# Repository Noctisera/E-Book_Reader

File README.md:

# OpenBook Reader

## 📘 Introduction  
**OpenBook Reader** is an open-source hardware project focused on delivering a practical, low-cost e-book device. Its primary aim is to build the physical design assets—such as schematics, board layouts, and casing models—needed for manufacturing the device according to system-level specs.

This initiative includes:
- Circuit design and layout.
- PCB preparation for fabrication.
- CAD models for enclosure and hardware integration.

---

## 🔧 Project Contents

This repository contains everything needed to bring the device to life, from electronics to mechanical files. Key folders include:

- **Electronics Design**
  - Circuit schematics  
  - Board layout data  
- **Fabrication Files**
  - Manufacturing exports (e.g., Gerbers)  
  - Assembly references (e.g., BOM, placement files)  
- **CAD Assets**
  - Mechanical parts in 3D format (STEP, Fusion360)  
- **Miscellaneous**
  - Licensing information  
  - Documentation  

---

## 📦 Components Summary

### Block Diagram

Below is a selection of the main components used in the hardware design. For each, you’ll find supplier and datasheet links for reference.

## Bill of Materials (BOM)

| Component                       | Link                                                                                                | Datasheet                                                                                             |
| :------------------------------ | :-------------------------------------------------------------------------------------------------- | :------------------------------------------------------------------------------------------------------ |
| ESP32-C6 WROOM-1-N8             | [SnapMagic](https://www.snapeda.com/parts/ESP32-C6-WROOM-1-N8/Espressif+Systems/view-part/?ref=eda) | [Datasheet](https://www.snapeda.com/parts/ESP32-C6-WROOM-1-N8/Espressif%20Systems/datasheet/)       |
| ESP32C6 Varistor 1812           | [Mouser](https://ro.mouser.com/ProductDetail/EPCOS-TDK/B72520T0350K062?qs=dEfas%2FXlABIszF52uu7vrg%3D%3D) | [Datasheet](https://www.tdk-electronics.tdk.com/inf/75/db/CTVS_14/Surge_protection_series.pdf)     |
| ESP32 WROVER 0805 Capacitor     | [Mouser](https://ro.mouser.com/ProductDetail/KYOCERA-AVX/SD0805S020S1R0?qs=jCA%252BPfw4LHbpkAoSnwrdjw%3D%3D) | [Datasheet](https://ro.mouser.com/datasheet/2/40/schottky-3165252.pdf)                               |
| ESP32 WROVER BME680 Sensor      | [SnapMagic](https://www.snapeda.com/parts/BME680/Bosch/view-part/?welcome=home)                      | [Datasheet](https://www.snapeda.com/parts/BME680/Bosch%20Sensortec/datasheet/)                           |
| ESP32 WROVER MCP73831 Power Management | [Mouser](https://eu.mouser.com/ProductDetail/Microchip-Technology/MCP73831T-2ACI-OT?qs=yUQqVecv4qvbBQBGbHx0Mw%3D%3D) | [Datasheet](https://eu.mouser.com/datasheet/2/268/MCP73831_Family_Data_Sheet_DS20001984H-3441711.pdf) |
| ESP32 WROVER P-Channel MOSFET   | [Component Search Engine](https://componentsearchengine.com/part-view/DMG2305UX-7/Diodes%20Incorporated) | [Datasheet](https://www.diodes.com//assets/Datasheets/DMG2305UX.pdf)                                  |
| LED Chip 0603                   | [SnapMagic](https://www.snapeda.com/parts/KP-1608SURCK/Kingbright/view-part/?ref=search&t=LED%200603) | [Datasheet](https://www.snapeda.com/parts/KP-1608SURCK/Kingbright/datasheet/)                           |
| SJ                              | [GrabCad](https://grabcad.com/library/solder-jumpers-1)                                             | [Datasheet](https://www.youtube.com/watch?v=dQw4w9WgXcQ)                                                 |
| LTSPICE Resistor 0402           | [Component Search Engine](https://componentsearchengine.com/part-view/R0402%201%25%20100%20K%20(RC0402FR-07100KL)/YAGEO) | [Datasheet](https://www.yageo.com/upload/media/product/products/datasheet/rchip/PYu-RC_Group_51_RoHS_L_12.pdf) |
| RCL CPOL 3528                   | [SnapMagic](https://www.snapeda.com/parts/TAJB475K025RNJ/AVX/view-part/?ref=dk&t=capacitor%203528&con_ref=None) | [Datasheet](https://s3.amazonaws.com/snapeda/datasheet/TAJB475K025RNJ_AVX.pdf)                       |
| 112A-TAAR-R03                   | [Comet](https://store.comet.srl.ro/Catalogue/Product/43497/)                                       | [Datasheet](https://store.comet.bg/download-file.php?id=27596)                                       |
| Capacitor 0402                  | [Component Search Engine](https://componentsearchengine.com/part-view/CC0402MRX5R5BB106/YAGEO)      | [Datasheet](https://componentsearchengine.com/Datasheets/2/CC0402MRX5R5BB106.pdf)                      |
| 744043680 IND                   | [Mouser](https://eu.mouser.com/ProductDetail/Wurth-Elektronik/744043680?qs=PGXP4M47uW6VkZq%252BkzjrHA%3D%3D) | [Datasheet](https://www.we-online.com/components/products/datasheet/744043680.pdf)                   |
| BD5229G-TR                      | [Component Search Engine](https://componentsearchengine.com/part-view/BD5229G-TR/ROHM%20Semiconductor) | [Datasheet](https://datasheet.datasheetarchive.com/originals/distributors/Datasheets_SAMA/f2b9741ef86007909f138d561a359946.pdf) |
| Custom Button                   | [Panasonic](https://industry.panasonic.com/global/en/products/control/switch/light-touch/number/evqpuj02k) | [Datasheet](https://industry.panasonic.com/global/en/downloads?tab=catalog&small_g_cd=203&part_no=EVQPUJ02K&q=RVZRUFVKMDJLJTdDMTMlN0MyMDMlN0MzNDU5JTdDMSU3QyU3QzIlN0M%3D) |
| CPH3225A                        | [SnapMagic](https://www.snapeda.com/parts/CPH3225A/Seiko+Instruments/view-part/?ref=eda)           | [Datasheet](https://www.snapeda.com/parts/CPH3225A/Seiko%20Instruments/datasheet/)                       |
| DS3231SN RTC                    | [SnapMagic](https://www.snapeda.com/parts/DS3231SN%23/Analog+Devices/view-part/?ref=eda)          | [Datasheet](https://www.snapeda.com/parts/DS3231SN%23/Analog%20Devices/datasheet/)                      |
| FH34SRJ-24S-0.5SH Connector     | [Component Search Engine](https://componentsearchengine.com/part-view/FH34SRJ-24S-0.5SH(99)/Hirose) | [Datasheet](https://www.hirose.com/en/product/document?clcode=CL0580-1255-6-99&productname=FH34SRJ-24S-0.5SH(99)&series=FH34SRJ&documenttype=2DDrawing&lang=en&documentid=0000990903) |
| MAX17048G+T10 Battery Fuel Gauge | [SnapMagic](https://www.snapeda.com/parts/MAX17048G+T10/Analog+Devices/view-part/?ref=eda)         | [Datasheet](https://www.snapeda.com/parts/MAX17048G+T10/Analog%20Devices/datasheet/)                    |
| MBR0530 Schottky Diode         | [SnapMagic](https://www.snapeda.com/parts/MBR0530/Onsemi/view-part/?ref=eda)                      | [Datasheet](https://www.snapeda.com/parts/MBR0530/ON%20Semiconductor/datasheet/)                         |
| PGB1010603MR Inductor          | [SnapMagic](https://www.snapeda.com/parts/PGB1010603MR/Littelfuse/view-part/?ref=eda)              | [Datasheet](https://www.snapeda.com/parts/PGB1010603MR/Littelfuse%20Inc./datasheet/)                     |
| QWIIC Connector                 | [Mouser](https://eu.mouser.com/ProductDetail/Adafruit/4208?qs=PzGy0jfpSMtbScLbr0L5dw%3D%3D)         | [Datasheet](https://www.youtube.com/watch?v=dQw4w9WgXcQ)                                                 |
| USB4110-GF-A USB Hub            | [Component Search Engine](https://componentsearchengine.com/part-view/USB4110-GF-A/GCT%20(GLOBAL%20CONNECTOR%20TECHNOLOGY)) | [Datasheet](https://gct.co/files/drawings/usb4110.pdf)                                                 |
| SI1308EDL-T1-GE3 MOSFET         | [SnapMagic](https://www.snapeda.com/parts/SI1308EDL-T1-GE3/Vishay+Siliconix/view-part/?ref=eda)   | [Datasheet](https://www.youtube.com/watch?v=dQw4w9WgXcQ)                                                 |
| TPTP20R                         | [Comet](https://easyeda.com/component/7524403feb2642ac9f9f26dfb93ceacf)                            | [Datasheet](https://easyeda.com/component/7524403feb2642ac9f9f26dfb93ceacf)                              |
| USBLC6-2SC6Y USB Surge Protection | [SnapMagic](https://www.snapeda.com/parts/USBLC6-2SC6Y/STMicroelectronics/view-part/?ref=eda)    | [Datasheet](https://www.snapeda.com/parts/USBLC6-2SC6Y/STMicroelectronics/datasheet/)                   |
| W25Q512JVEIQ Flash Memory       | [SnapMagic](https://www.snapeda.com/parts/W25Q512JVEIQ/Winbond+Electronics/view-part/?ref=eda)     | [Datasheet](https://www.snapeda.com/parts/W25Q512JVEIQ/Winbond%20Electronics/datasheet/)                |
| XC6220A331MR-G Voltage Regulator | [Component Search Engine](https://componentsearchengine.com/part-view/XC6220A331MR-G/Torex)      | [Datasheet](https://product.torexsemi.com/system/files/series/xc6220.pdf)                               |

---

## 🧠 Key Modules and Functionality

### 🟡 Power System  
- **Battery:** Rechargeable Li-Po providing 3.7V, 1800mAh capacity.  
- **Charger:** Manages safe charging through USB-C.  
- **Regulation:** LDOs provide clean power to different system sections.

### 🔲 Display Unit  
- **Type:** 7.5-inch e-paper screen (black & white).  
- **Comms:** SPI-based, ultra-low-power refresh.

### 🎛 Microcontroller  
- **Model:** ESP32-C6  
- **Role:** Central processor managing all I/O, display, memory, and sensors.  
- **Connectivity:** Offers Wi-Fi and Bluetooth for syncing or updates.

### 🌦 Environmental Sensor  
- **Chip:** BME688  
- **Function:** Captures environmental data (temp, pressure, humidity, gas).

### 🕒 Real-Time Clock  
- **RTC:** DS3231  
- **Use Case:** Keeps time even without power—great for tracking usage.

### 💾 Storage  
- **Flash Memory:** For storing firmware and runtime data.  
- **SD Card Support:** Optional external storage for large file handling (e.g. e-books).

### 🧩 Expandability  
- **Connectors:** I2C/SPI breakout headers support add-on modules.  
- **Test Points:** Available for programming, debugging, and diagnostics.

---

## 🔌 Interfaces & I/O

| Interface | Purpose |
|----------|---------|
| **SPI**  | Display, SD Card, Flash Memory |
| **I2C**  | Sensor, RTC |
| **USB-C**| Charging & data |
| **GPIO** | Button inputs, status indicators |

---

## 📃 License  
This project is released under the MIT License—feel free to use, remix, and contribute.

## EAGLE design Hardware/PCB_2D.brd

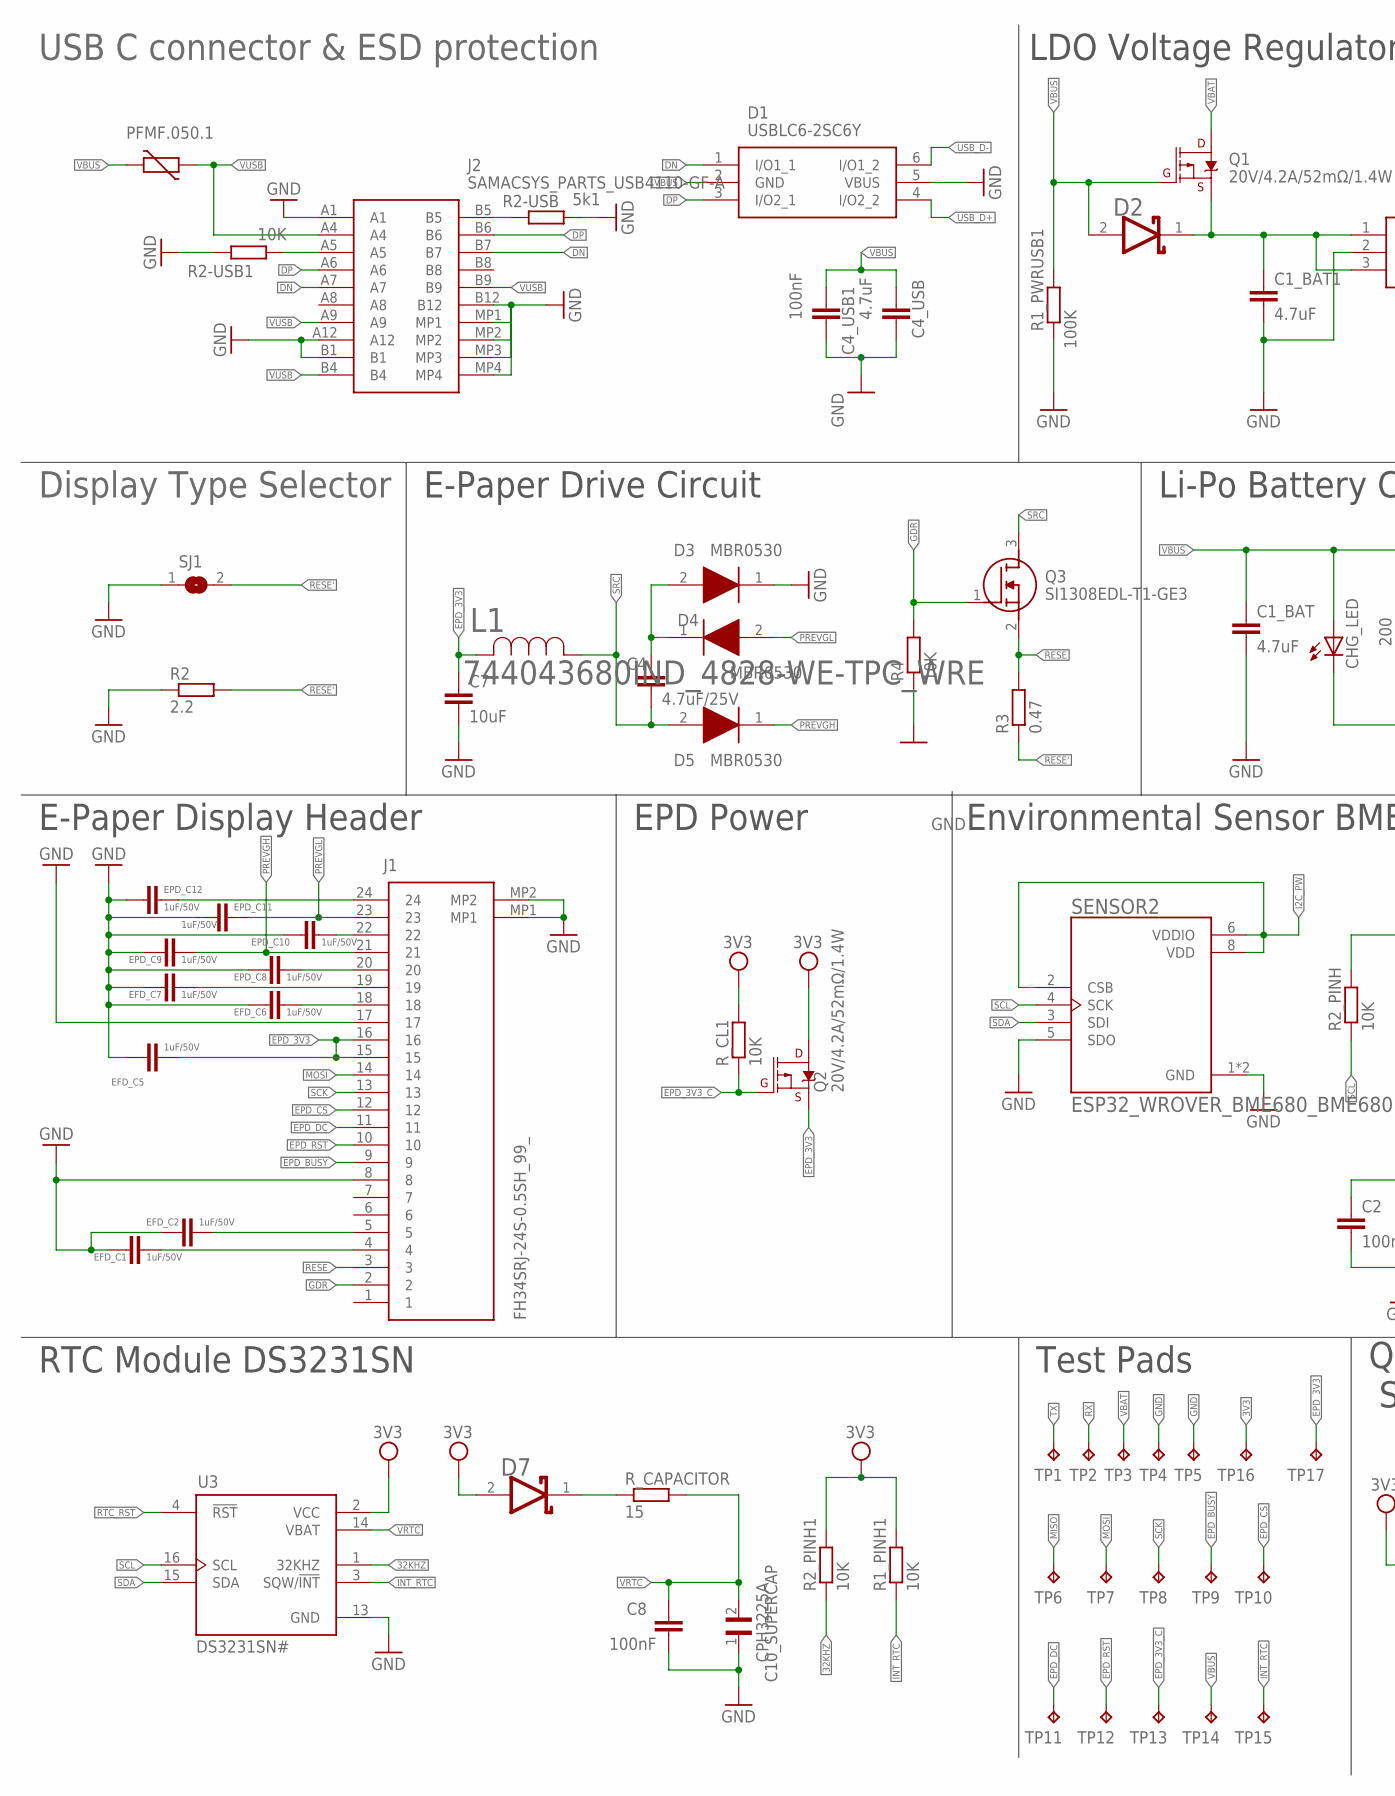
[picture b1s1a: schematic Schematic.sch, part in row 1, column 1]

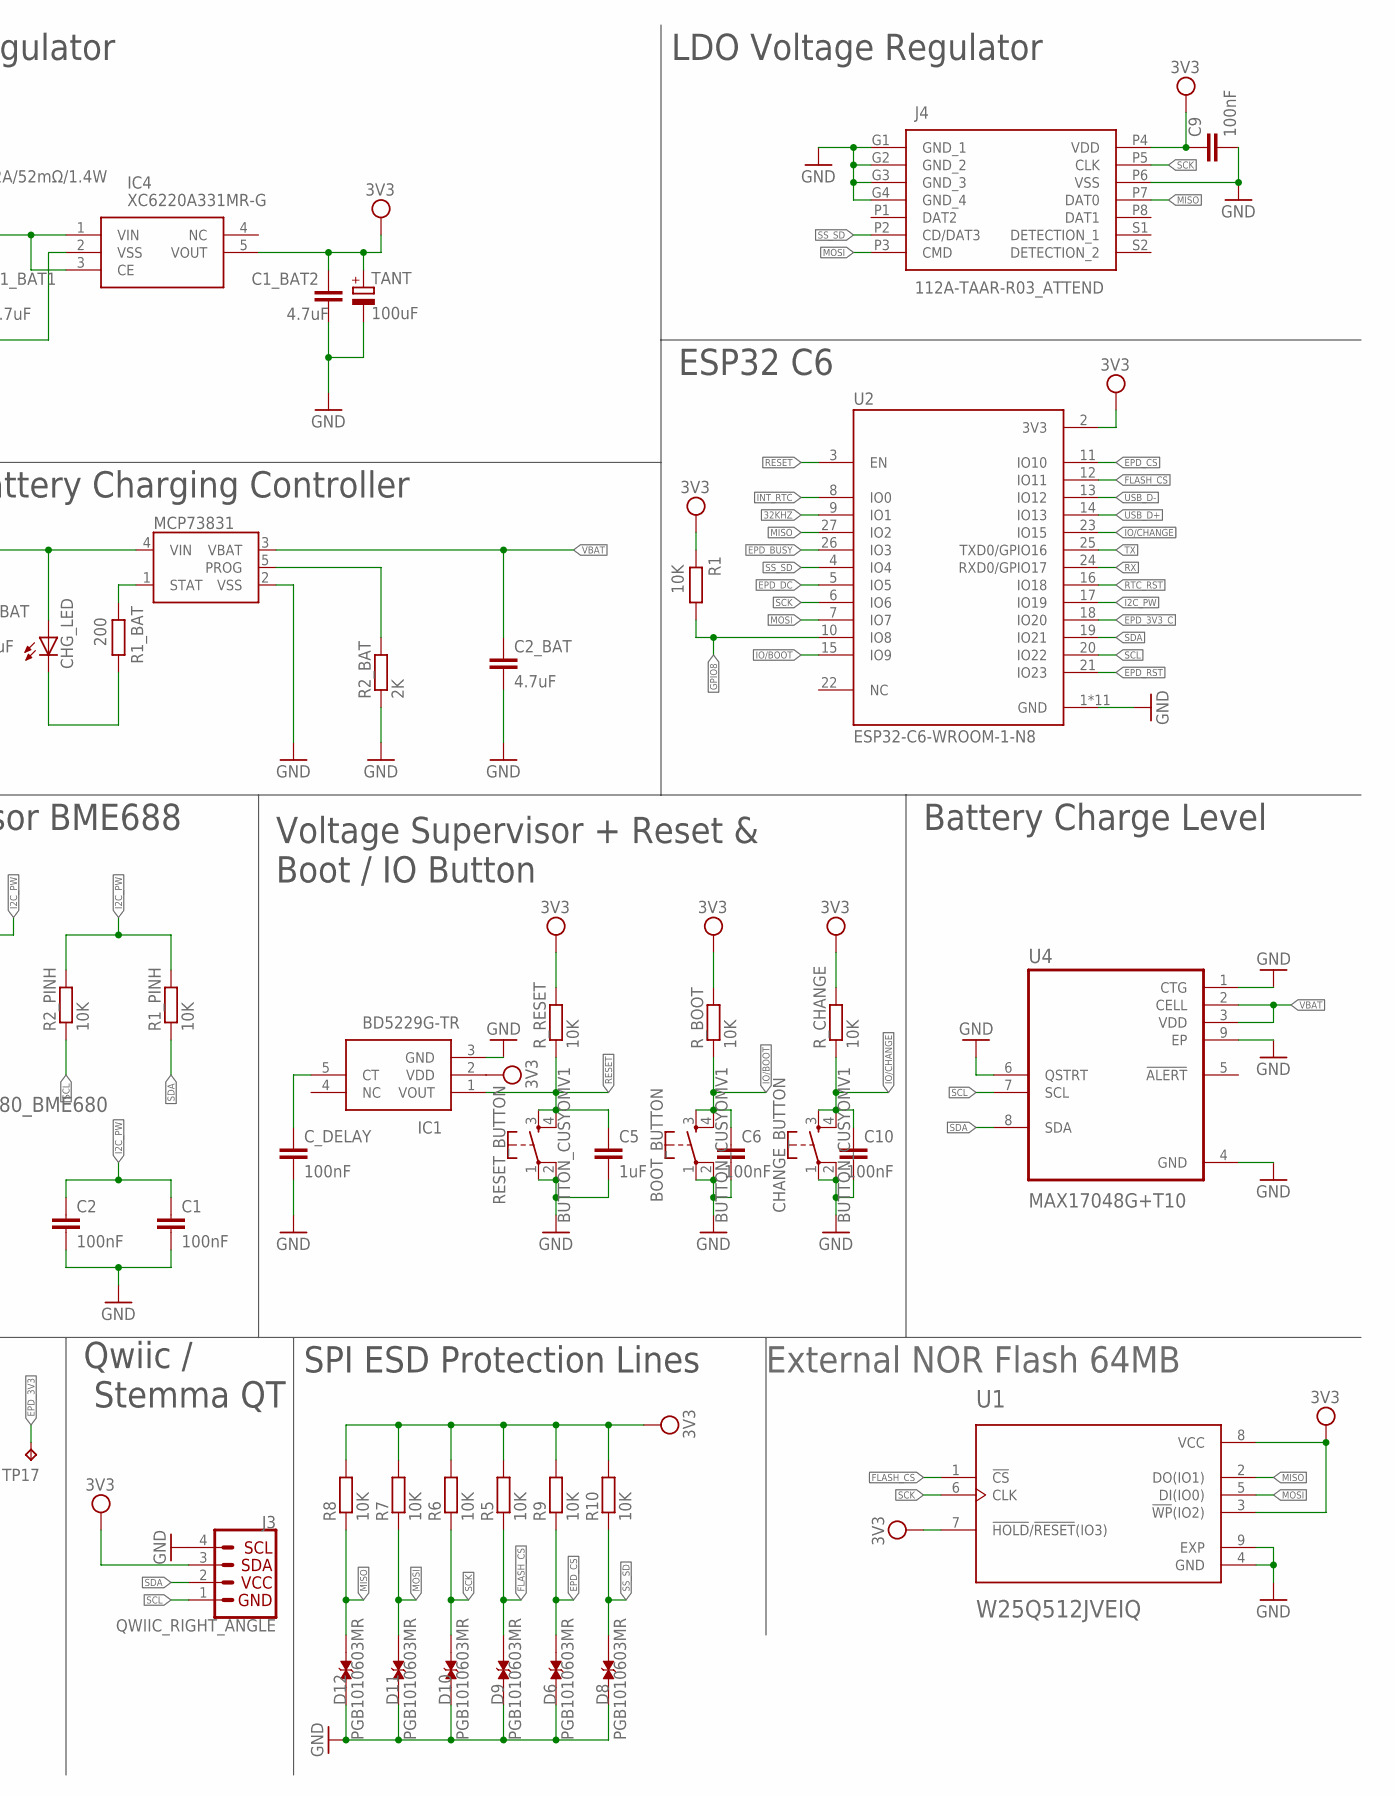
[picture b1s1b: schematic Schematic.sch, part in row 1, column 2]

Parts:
BOOT_BUTTON: BUTTON_CUSYOMV1; MYBUTTON
C1, C2, C4_USB1, C6, C8, C9, C10: 100nF; EAGLE-LTSPICE_C0402
C1_BAT, C1_BAT1, C1_BAT2, C2_BAT, C4_USB: 4.7uF; EAGLE-LTSPICE_C0402
C4: 4.7uF/25V; EAGLE-LTSPICE_C0402
C5: 1uF; EAGLE-LTSPICE_C0402
C7: 10uF; EAGLE-LTSPICE_C0402
C10_SUPERCAP: CPH3225A; CAPCP3225X100N
CHANGE_BUTTON: BUTTON_CUSYOMV1; MYBUTTON
CHG_LED: ADAFRUIT_CHIP-LED0603
C_DELAY: 100nF; EAGLE-LTSPICE_C0402
D1: USBLC6-2SC6Y; SOT95P280X145-6N
D2, D7: ESP32_WROVER_AVX---SD0805S020S1R0_AVX_SD0805S020S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; ESP32_WROVER_AVX---SD0805S020S1R0_AVX_SD0805S020S1R0_0
D3, D4, D5: MBR0530; SOD3716X135N
D6, D8, D9, D10, D11, D12: PGB1010603MR; DIOC1608X36N
EFD_C1, EFD_C2, EFD_C5, EFD_C6, EFD_C7: 1uF/50V; EAGLE-LTSPICE_C0402
EPD_C8, EPD_C9, EPD_C10, EPD_C11, EPD_C12: 1uF/50V; EAGLE-LTSPICE_C0402
IC1: BD5229G-TR; SOT95P280X125-5N
IC4: XC6220A331MR-G; SOT95P280X120-5N
J1: FH34SRJ-24S-0.5SH_99_; FH34SRJ24S05SH99
J2: SAMACSYS_PARTS_USB4110-GF-A; SAMACSYS_PARTS_USB4110GFA
J3: QWIIC_RIGHT_ANGLE; JST04_1MM_RA
J4: 112A-TAAR-R03_ATTEND; 112ATAARR03ATTEND
L1: 744043680IND_4828-WE-TPC_WRE; IND_4828-WE-TPC_WRE
MCP73831: ESP32_WROVER_SPARKFUN-IC-POWER_MCP73831; ESP32_WROVER_SPARKFUN-IC-POWER_SOT23-5
PFMF.050.1: ESP32C6_VARISTORCN1812; ESP32C6_VARISTOR_CT/CN1812
Q1, Q2: 20V/4.2A/52mΩ/1.4W; ESP32_WROVER_SPARKFUN-DISCRETESEMI_SOT23-3
Q3: SI1308EDL-T1-GE3; SOT65P210X110-3N
R1, R1_PINH, R1_PINH1, R2-USB1, R2_PINH, R2_PINH1, R4, R5, R6, R7, R8, R9, R10: 10K; ESP32_WROVER_EAGLE-LTSPICE_R0402
R1_BAT: 200; ESP32_WROVER_EAGLE-LTSPICE_R0402
R1_PWRUSB1: 100K; ESP32_WROVER_EAGLE-LTSPICE_R0402
R2: 2.2; ESP32_WROVER_EAGLE-LTSPICE_R0402
R2-USB: 5k1; ESP32_WROVER_EAGLE-LTSPICE_R0402
R2_BAT: 2K; ESP32_WROVER_EAGLE-LTSPICE_R0402
R3: 0.47; ESP32_WROVER_EAGLE-LTSPICE_R0402
RESET_BUTTON: BUTTON_CUSYOMV1; MYBUTTON
R_BOOT: 10K; ESP32_WROVER_EAGLE-LTSPICE_R0402
R_CAPACITOR: 15; ESP32_WROVER_EAGLE-LTSPICE_R0402
R_CHANGE: 10K; ESP32_WROVER_EAGLE-LTSPICE_R0402
R_CL1: 10K; ESP32_WROVER_EAGLE-LTSPICE_R0402
R_RESET: 10K; ESP32_WROVER_EAGLE-LTSPICE_R0402
SENSOR2: ESP32_WROVER_BME680_BME680; ESP32_WROVER_BME680_PSON80P300X300X100-8N
SJ1: SJ
TANT: 100uF; RCL_CT3528
TP1, TP2, TP3, TP4, TP5, TP6, TP7, TP8, TP9, TP10, TP11, TP12, TP13, TP14, TP15, TP16, TP17: TPTP20R; TP20R
U1: W25Q512JVEIQ; SON127P600X800X80-9N
U2: ESP32-C6-WROOM-1-N8; XCVR_ESP32-C6-WROOM-1-N8
U3: DS3231SN#; SOIC127P1032X265-16N
U4: MAX17048G+T10; SON50P200X200X80-9N

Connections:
3V3: C1_BAT2.1, C9.1, D7.2 (ANODE), IC1.2 (VDD), IC4.5 (VOUT), J3.3, J4.P4 (VDD), Q2.3 (D), R1.2, R1_PINH1.2, R2_PINH1.2, R5.2, R6.2, R7.2, R8.2, R9.2, R10.2, R_BOOT.2, R_CHANGE.2, R_CL1.2, R_RESET.2, TANT.+, TP16.TP, U1.3 (!WP!(IO2)), U1.7 (!HOLD!/!RESET!(IO3)), U1.8 (VCC), U2.2 (3V3), U3.2 (VCC)
32KHZ: R2_PINH1.1, U2.9 (IO1), U3.1 (32KHZ)
DN: D1.1 (I/O1_1), J2.A7, J2.B7
DP: D1.3 (I/O2_1), J2.A6, J2.B6
EPD_3V3: C7.1, EFD_C5.1, J1.15, J1.16, L1.2, Q2.2 (S), TP17.TP
EPD_3V3_C: Q2.1 (G), R_CL1.1, TP13.TP, U2.18 (IO20)
EPD_BUSY: J1.9, TP9.TP, U2.26 (IO3)
EPD_CS: D6.2, J1.12, R9.1, TP10.TP, U2.11 (IO10)
EPD_DC: J1.11, TP11.TP, U2.5 (IO5)
EPD_RST: J1.10, TP12.TP, U2.21 (IO23)
FLASH_CS: D9.2, R5.1, U1.1 (!CS), U2.12 (IO11)
GDR: J1.2, Q3.1 (G), R4.2
GND: BOOT_BUTTON.1, BOOT_BUTTON.2, C1.2, C1_BAT.2, C1_BAT1.2, C1_BAT2.2, C2.2, C2_BAT.2, C4_USB.2, C4_USB1.2, C5.2, C6.2, C7.2, C8.2, C9.2, C10.2, C10_SUPERCAP.1, CHANGE_BUTTON.1, CHANGE_BUTTON.2, C_DELAY.2, D1.5 (VBUS), D3.1 (K), D6.1, D8.1, D9.1, D10.1, D11.1, D12.1, EFD_C1.2, EFD_C2.2, EFD_C5.2, EFD_C6.2, EFD_C7.2, EPD_C8.2, EPD_C9.2, EPD_C10.2, EPD_C11.2, EPD_C12.2, IC1.3 (GND), IC4.2 (VSS), J1.8, J1.17, J1.MP1, J1.MP2, J2.A1, J2.A12, J2.B1, J2.B12, J2.MP1, J2.MP2, J2.MP3, J2.MP4, J3.4, J4.G1 (GND_1), J4.G2 (GND_2), J4.G3 (GND_3), J4.G4 (GND_4), J4.P6 (VSS), MCP73831.2 (VSS), R1_PWRUSB1.1, R2.1, R2-USB.2, R2-USB1.1, R2_BAT.1, R4.1, RESET_BUTTON.1, RESET_BUTTON.2, SENSOR2.1 (GND), SENSOR2.5 (SDO), SENSOR2.7 (GND), SJ1.1, TANT.-, TP4.TP, TP5.TP, U1.4 (GND), U1.9 (EXP), U2.1 (GND), U2.28 (GND), U2.29_1 (GND), U2.29_2 (GND), U2.29_3 (GND), U2.29_4 (GND), U2.29_5 (GND), U2.29_6 (GND), U2.29_7 (GND), U2.29_8 (GND), U2.29_9 (GND), U3.13 (GND), U4.1 (CTG), U4.4 (GND), U4.6 (QSTRT), U4.9 (EP)
GPIO8: R1.1, U2.10 (IO8)
I2C_PW: C1.1, C2.1, R1_PINH.2, R2_PINH.2, SENSOR2.2 (CSB), SENSOR2.6 (VDDIO), SENSOR2.8 (VDD), U2.17 (IO19)
INT_RTC: R1_PINH1.1, TP15.TP, U2.8 (IO0), U3.3 (SQW/!INT)
IO/BOOT: BOOT_BUTTON.3, BOOT_BUTTON.4, C6.1, R_BOOT.1, U2.15 (IO9)
IO/CHANGE: C10.1, CHANGE_BUTTON.3, CHANGE_BUTTON.4, R_CHANGE.1, U2.23 (IO15)
MISO: D12.2, J4.P7 (DAT0), R8.1, TP6.TP, U1.2 (DO(IO1)), U2.27 (IO2)
MOSI: D11.2, J1.14, J4.P3 (CMD), R7.1, TP7.TP, U1.5 (DI(IO0)), U2.7 (IO7)
unnamed: J2.B5, R2-USB.1
unnamed: C1_BAT1.1, D2.1 (CATHODE), IC4.1 (VIN), IC4.3 (CE), Q1.2 (S)
unnamed: MCP73831.1 (STAT), R1_BAT.2
unnamed: CHG_LED.C, R1_BAT.1
unnamed: MCP73831.5 (PROG), R2_BAT.2
unnamed: C_DELAY.1, IC1.5 (CT)
unnamed: C4.1, D3.2 (A), D4.1 (K)
unnamed: J2.A5, R2-USB1.2
unnamed: D7.1 (CATHODE), R_CAPACITOR.1
unnamed: EFD_C2.1, J1.5
unnamed: EFD_C1.1, J1.4
unnamed: EPD_C12.1, J1.24
unnamed: EPD_C10.1, J1.22
unnamed: EPD_C8.1, J1.20
unnamed: EFD_C7.1, J1.19
unnamed: EFD_C6.1, J1.18
PREVGH: D5.1 (K), EPD_C9.1, J1.21
PREVGL: D4.2 (A), EPD_C11.1, J1.23
RESE: J1.3, Q3.2 (S), R3.2
RESE': R2.2, R3.1, SJ1.2
RESET: C5.1, IC1.1 (VOUT), RESET_BUTTON.3, RESET_BUTTON.4, R_RESET.1, U2.3 (EN)
RTC_RST: U2.16 (IO18), U3.4 (!RST)
RX: TP2.TP, U2.24 (RXD0/GPIO17)
SCK: D10.2, J1.13, J4.P5 (CLK), R6.1, TP8.TP, U1.6 (CLK), U2.6 (IO6)
SCL: J3.1, R2_PINH.1, SENSOR2.4 (SCK), U2.20 (IO22), U3.16 (SCL), U4.7 (SCL)
SDA: J3.2, R1_PINH.1, SENSOR2.3 (SDI), U2.19 (IO21), U3.15 (SDA), U4.8 (SDA)
SRC: C4.2, D5.2 (A), L1.1, Q3.3 (D)
SS_SD: D8.2, J4.P2 (CD/DAT3), R10.1, U2.4 (IO4)
TX: TP1.TP, U2.25 (TXD0/GPIO16)
USB_D+: D1.4 (I/O2_2), U2.14 (IO13)
USB_D-: D1.6 (I/O1_2), U2.13 (IO12)
VBAT: C2_BAT.1, MCP73831.3 (VBAT), Q1.3 (D), TP3.TP, U4.2 (CELL), U4.3 (VDD)
VBUS: C1_BAT.1, C4_USB.1, C4_USB1.1, CHG_LED.A, D1.2 (GND), D2.2 (ANODE), MCP73831.4 (VIN), PFMF.050.1.2, Q1.1 (G), R1_PWRUSB1.2, TP14.TP
VRTC: C8.1, C10_SUPERCAP.2, R_CAPACITOR.2, U3.14 (VBAT)
VUSB: J2.A4, J2.A9, J2.B4, J2.B9, PFMF.050.1.1

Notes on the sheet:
USB C connector & ESD protection
LDO Voltage Regulator
Display Type Selector
E-Paper Drive Circuit
Li-Po Battery Charging Controller
E-Paper Display Header
EPD Power
Environmental Sensor BME688
ESP32 C6
Voltage Supervisor + Reset & Boot / IO Button
Battery Charge Level
RTC Module DS3231SN
Test Pads
Qwiic / Stemma QT
SPI ESD Protection Lines
External NOR Flash 64MB

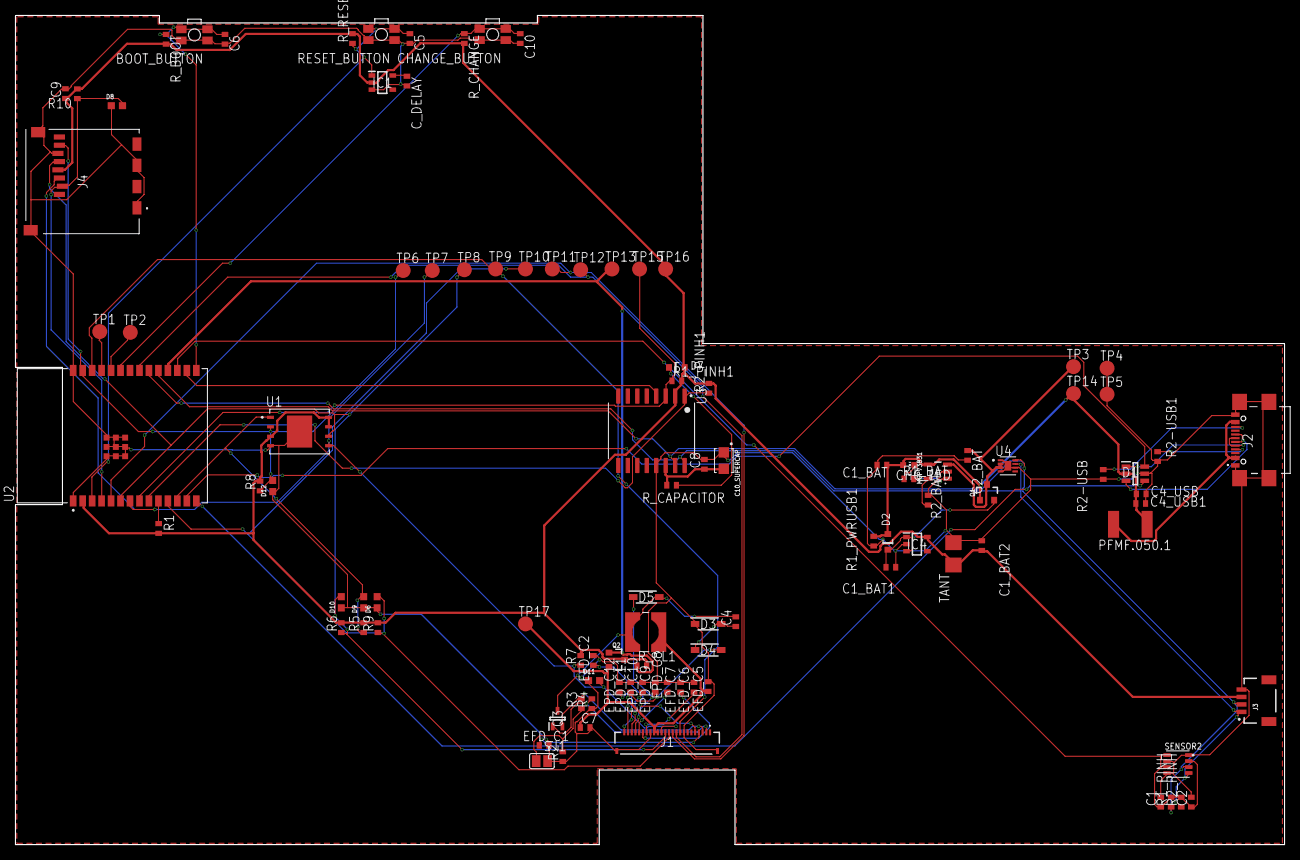
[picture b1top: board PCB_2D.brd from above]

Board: 2 copper layers, 170.2 x 111.2 mm, 103 parts (0 on the bottom side), 55 nets.

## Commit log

2025-04-06 Create LICENSE
2025-04-06 Last files
2025-04-06 Changed
2025-04-06 Rename Burger_View.step to Exploded_View.step
2025-04-14 Fixed issues

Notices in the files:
parts and their libraries:
COPYRIGHT: Copyright (C) 2024 Ultra Librarian. All rights reserved.
